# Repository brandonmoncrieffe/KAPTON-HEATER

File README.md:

## Kapton Heater System for Oxidizer Tank Pressure Regulation

This system uses a 24V, 14.6A Kapton trace heater to regulate the pressure inside a nitrous oxide oxidizer tank, particularly in colder environments where vapor pressure drops below optimal levels. The heater is PWM-controlled via a high-current N-channel MOSFET, allowing for precise thermal regulation.

Designed by Brandon Moncriefe and Aslan Lauzon for QRET

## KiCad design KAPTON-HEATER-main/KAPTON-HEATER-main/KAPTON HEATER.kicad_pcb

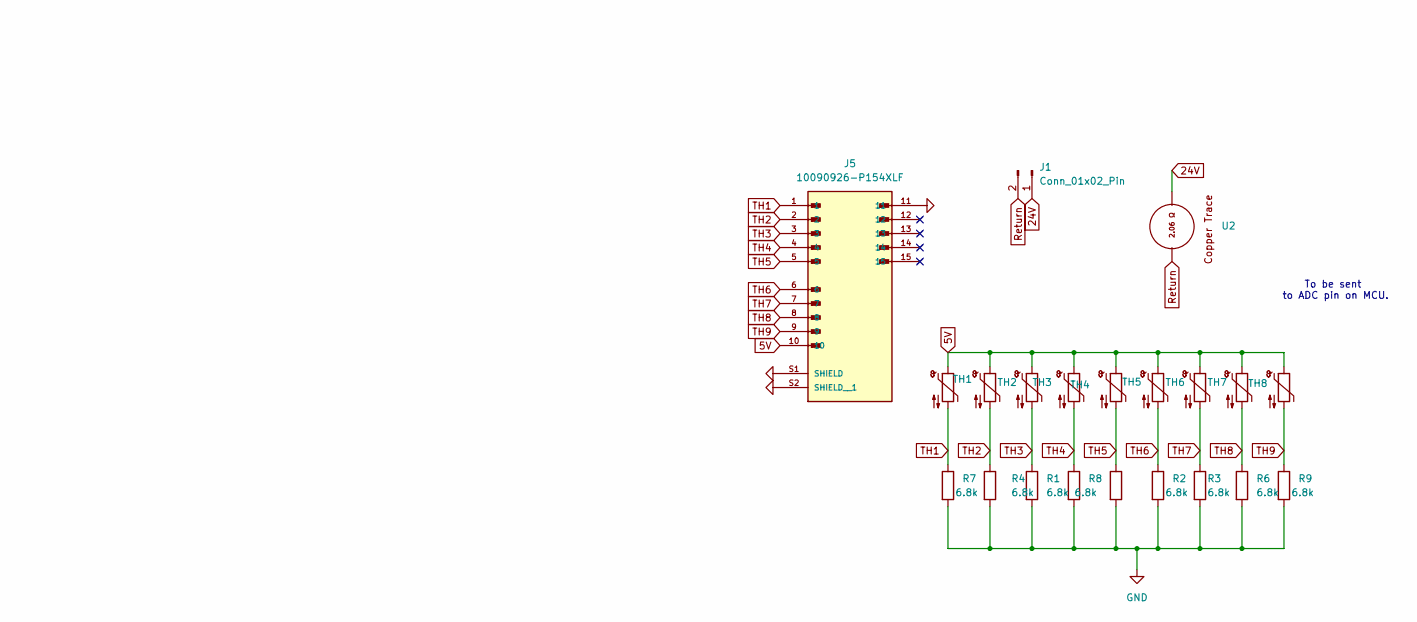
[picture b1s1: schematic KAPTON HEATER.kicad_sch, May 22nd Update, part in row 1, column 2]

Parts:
J1: Conn_01x02_Pin; AMASS_XT60PW-M
J5: 10090926-P154XLF; AMPHENOL_10090926-P154XLF; PARTREV H
R1, R2, R3, R4, R5, R6, R7, R8, R9: 6.8k; R_0201_0603Metric
TH1, TH2, TH3, TH4, TH5, TH6, TH7, TH8, TH9: Thermistor_NTC; R_0402_1005Metric
U2: (no value)

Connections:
5V: J5.10, TH1.1, TH2.1, TH3.1, TH4.1, TH5.1, TH6.1, TH7.1, TH8.1, TH9.1
24V: J1.1 (S1), U2.
GND: J5.11, J5.S1 (SHIELD), J5.S2 (SHIELD__1), R1.2, R2.2, R3.2, R4.2, R5.2, R6.2, R7.2, R8.2, R9.2
Return: J1.2 (S2), U2.
TH1: J5.1, R7.1, TH1.2
TH2: J5.2, R4.1, TH2.2
TH3: J5.3, R1.1, TH3.2
TH4: J5.4, R8.1, TH4.2
TH5: J5.5, R5.1, TH5.2
TH6: J5.6, R2.1, TH6.2
TH7: J5.7, R3.1, TH7.2
TH8: J5.8, R6.1, TH8.2
TH9: J5.9, R9.1, TH9.2

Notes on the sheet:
To be sent to ADC pin on MCU.

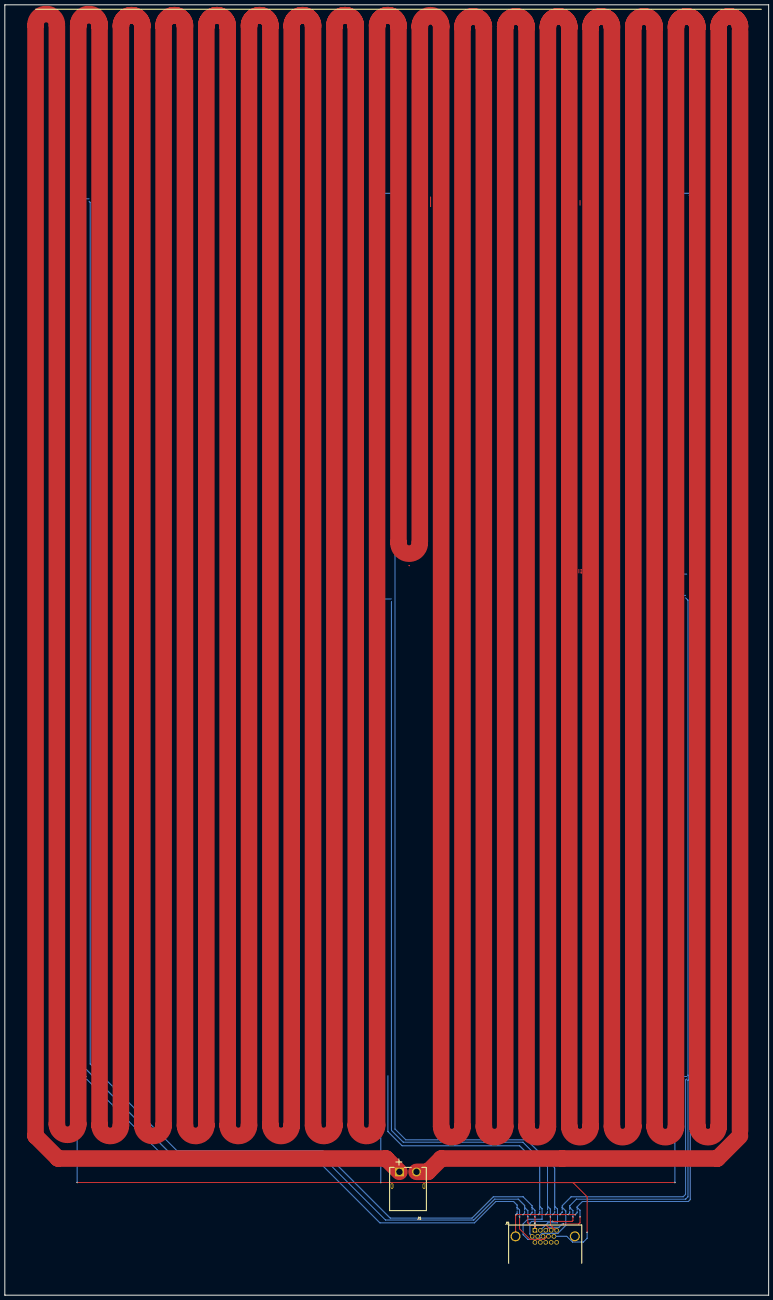
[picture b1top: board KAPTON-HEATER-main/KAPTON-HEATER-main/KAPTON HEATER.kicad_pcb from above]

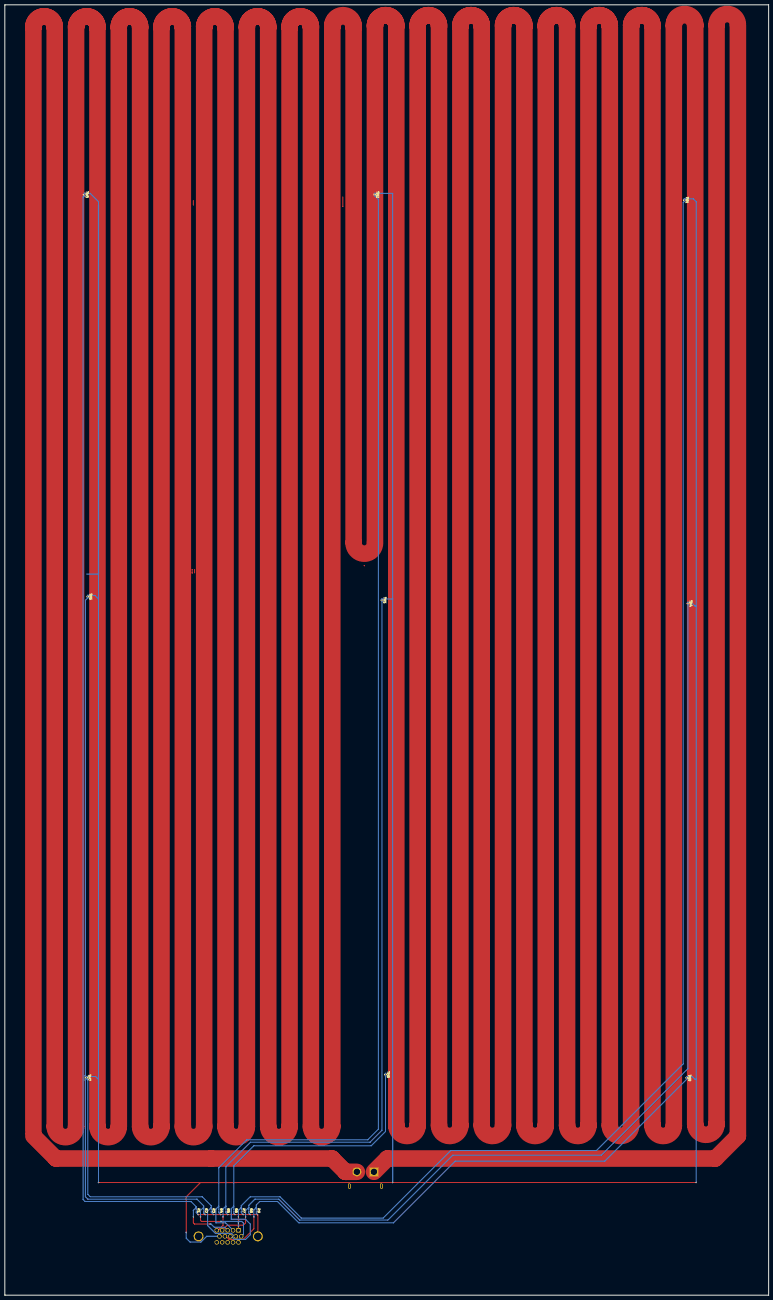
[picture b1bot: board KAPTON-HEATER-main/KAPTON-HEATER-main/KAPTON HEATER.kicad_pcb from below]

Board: 2 copper layers, 322.0 x 544.0 mm, 20 parts (18 on the bottom side), 11 nets.

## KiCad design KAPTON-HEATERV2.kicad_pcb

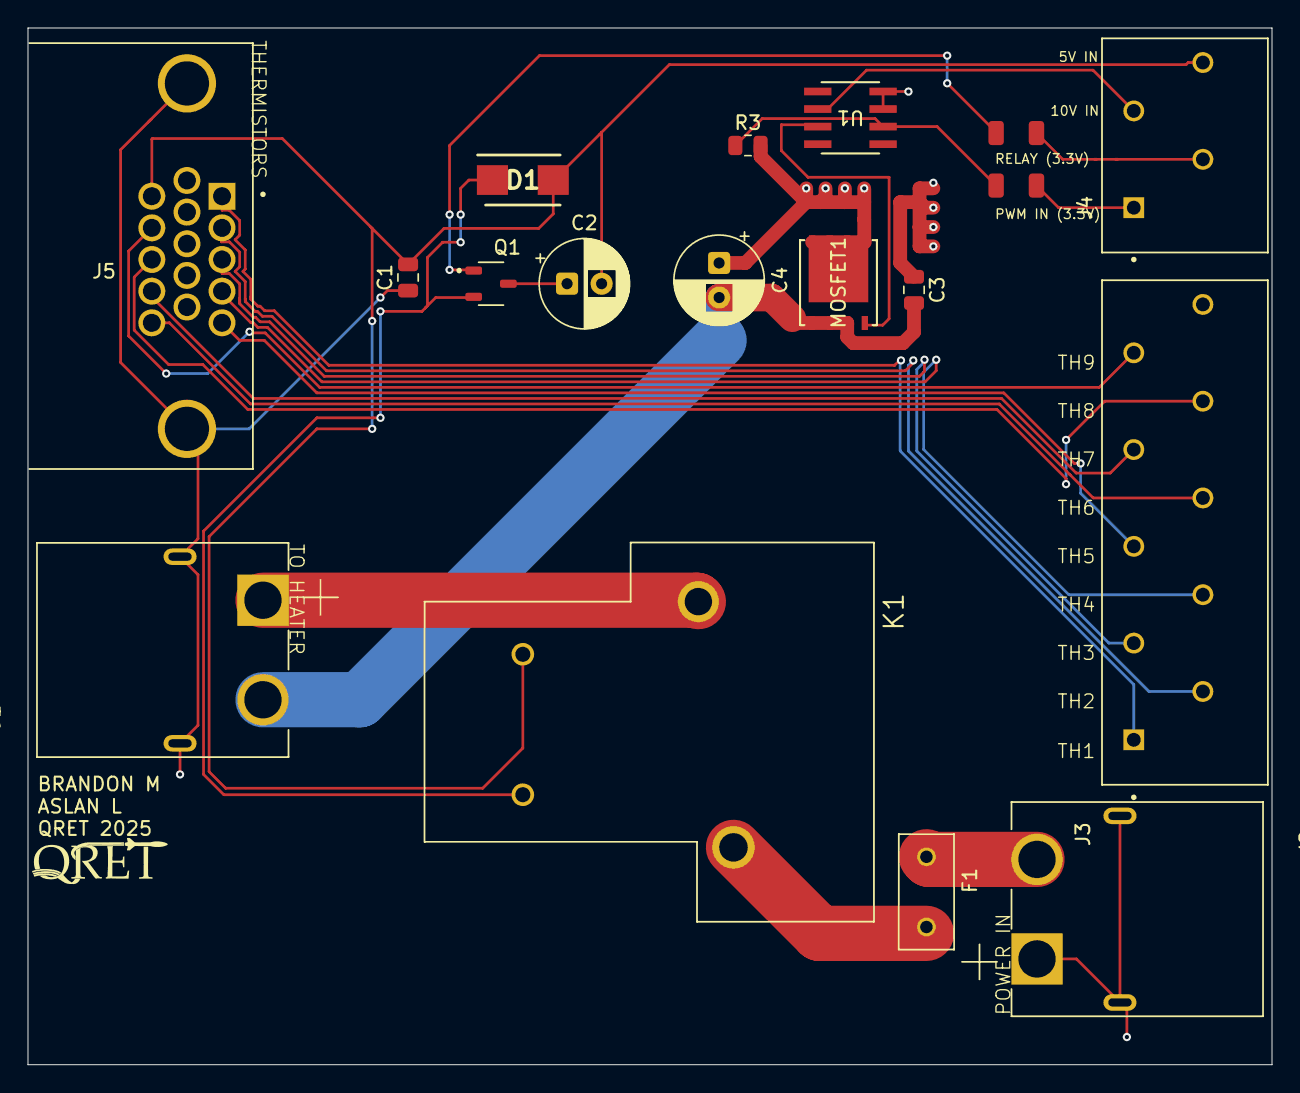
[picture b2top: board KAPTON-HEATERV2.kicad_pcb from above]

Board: 2 copper layers, 90.0 x 75.0 mm, 18 parts (0 on the bottom side), 22 nets.

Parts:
C1: C0.1uf; C_0805_2012Metric
C2: C47uf; CP_Radial_D6.3mm_P2.50mm
C3: C1uf; C_0805_2012Metric
C4: C10uf; CP_Radial_D6.3mm_P2.50mm
D1: MBRS1100T3G; DIOM5436X247N
F1: 20A Fuse; FUSRR508W60L835T400H810
J1, J2: XT60PW-M; AMASS_XT60PW-M
J3: 1985276; PHOENIX_1985276
J4: 1985218; TE_1985218
J5: 10090926-P154XLF; AMPHENOL_10090926-P154XLF
K1: 1-1393210-8; RELAY_1-1393210-8
MOSFET1: SIR462DP-T1-GE3; POWERPAK_SO-8_SINGLE_VIS
Q1: AO3400A; SOT95P280X125-3N
R1, R2: 100; R_1206
R3: R100k; R_0805_2012Metric
U1: TC4427ACOA; SOIC8-N_MC_MCH

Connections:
5V: C1.2, C2.2, D1.2 (A), J4.4, J5.11, K1.1
10V: J4.3, U1.6 (VDD)
10V PWM: MOSFET1.4, U1.7 (OUT_A)
/24V: J1.1, K1.4
/24VIN: F1.1, J2.2
/24VIN2: F1.2, K1.3
GND: C1.1, C2.1, C3.1, C4.1, J2.1, J2.S1, J2.S2, J5.S1 (SHIELD), J5.S2 (SHIELD__1), MOSFET1.5, MOSFET1.6, MOSFET1.7, MOSFET1.8, Q1.3, R3.2, U1.3 (GND), U1.4 (INPUT_B)
unnamed: D1.1 (K), K1.2, Q1.2
unnamed: C3.2, C4.2, J1.2, MOSFET1.1, MOSFET1.2, MOSFET1.3
unnamed: Q1.1, R1.2
unnamed: R2.2, R3.1, U1.2 (INPUT_A)
PWM: J4.1, R2.1
RELAY: J4.2, R1.1
TH1: J3.1, J5.1
TH2: J3.2, J5.2
TH3: J3.3, J5.3
TH4: J3.4, J5.4
TH5: J3.5, J5.5
TH6: J3.6, J5.15
TH7: J3.7, J5.14
TH8: J3.8, J5.13
TH9: J3.9, J5.12

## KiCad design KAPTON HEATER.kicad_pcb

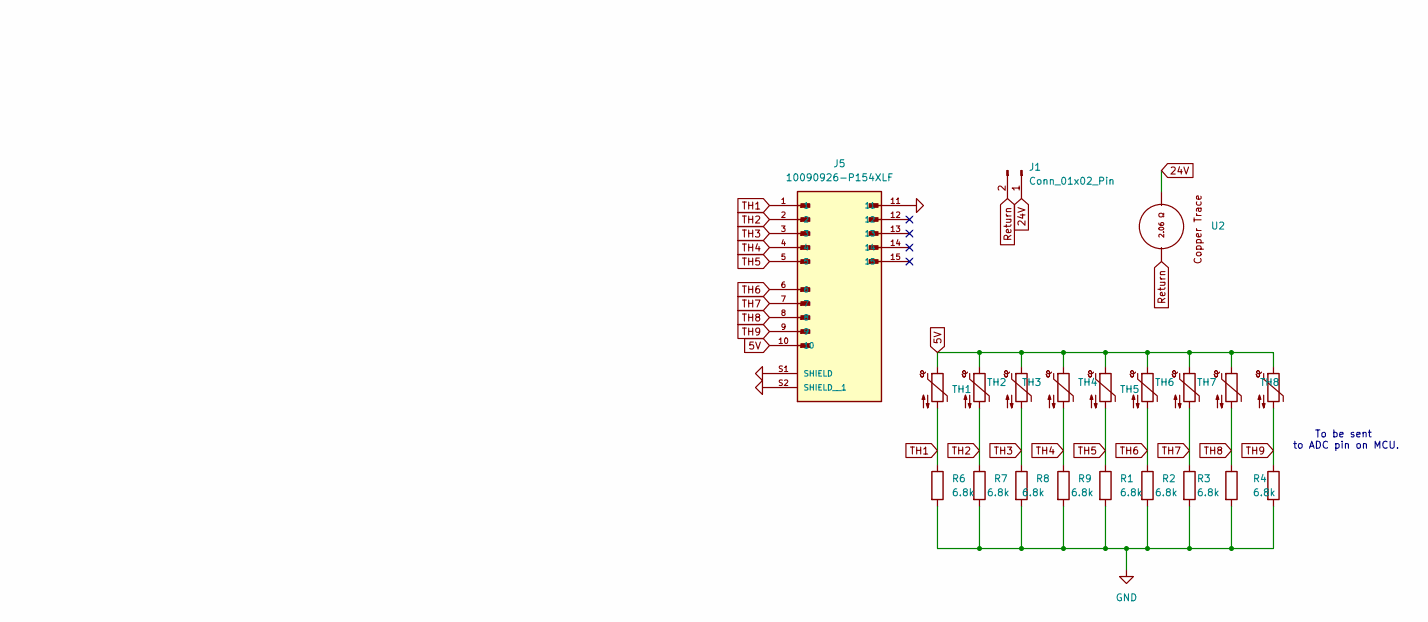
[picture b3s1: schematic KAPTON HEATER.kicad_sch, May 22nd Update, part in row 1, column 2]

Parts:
J1: Conn_01x02_Pin; AMASS_XT60PW-M
J5: 10090926-P154XLF; AMPHENOL_10090926-P154XLF; PARTREV H
R1, R2, R3, R4, R5, R6, R7, R8, R9: 6.8k; R_0201_0603Metric
TH1, TH2, TH3, TH4, TH5, TH6, TH7, TH8, TH9: Thermistor_NTC; R_Array_SIP4
U2: (no value)

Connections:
5V: J5.10, TH1.1, TH2.1, TH3.1, TH4.1, TH5.1, TH6.1, TH7.1, TH8.1, TH9.1
24V: J1.1 (S1), U2.
GND: J5.11, J5.S1 (SHIELD), J5.S2 (SHIELD__1), R1.2, R2.2, R3.2, R4.2, R5.2, R6.2, R7.2, R8.2, R9.2
Return: J1.2 (S2), U2.
TH1: J5.1, R6.1, TH1.2
TH2: J5.2, R7.1, TH2.2
TH3: J5.3, R8.1, TH3.2
TH4: J5.4, R9.1, TH4.2
TH5: J5.5, R1.1, TH5.2
TH6: J5.6, R2.1, TH6.2
TH7: J5.7, R3.1, TH7.2
TH8: J5.8, R4.1, TH8.2
TH9: J5.9, R5.1, TH9.2

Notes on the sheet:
To be sent to ADC pin on MCU.

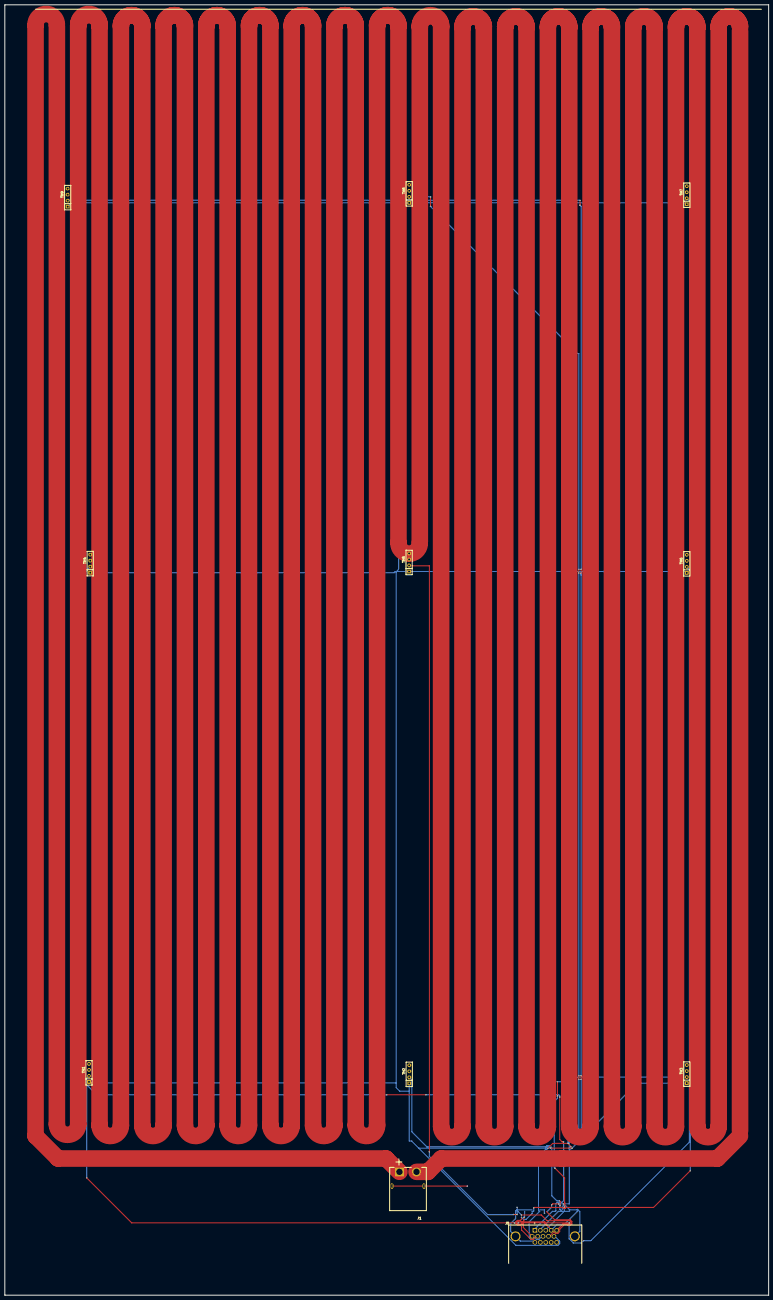
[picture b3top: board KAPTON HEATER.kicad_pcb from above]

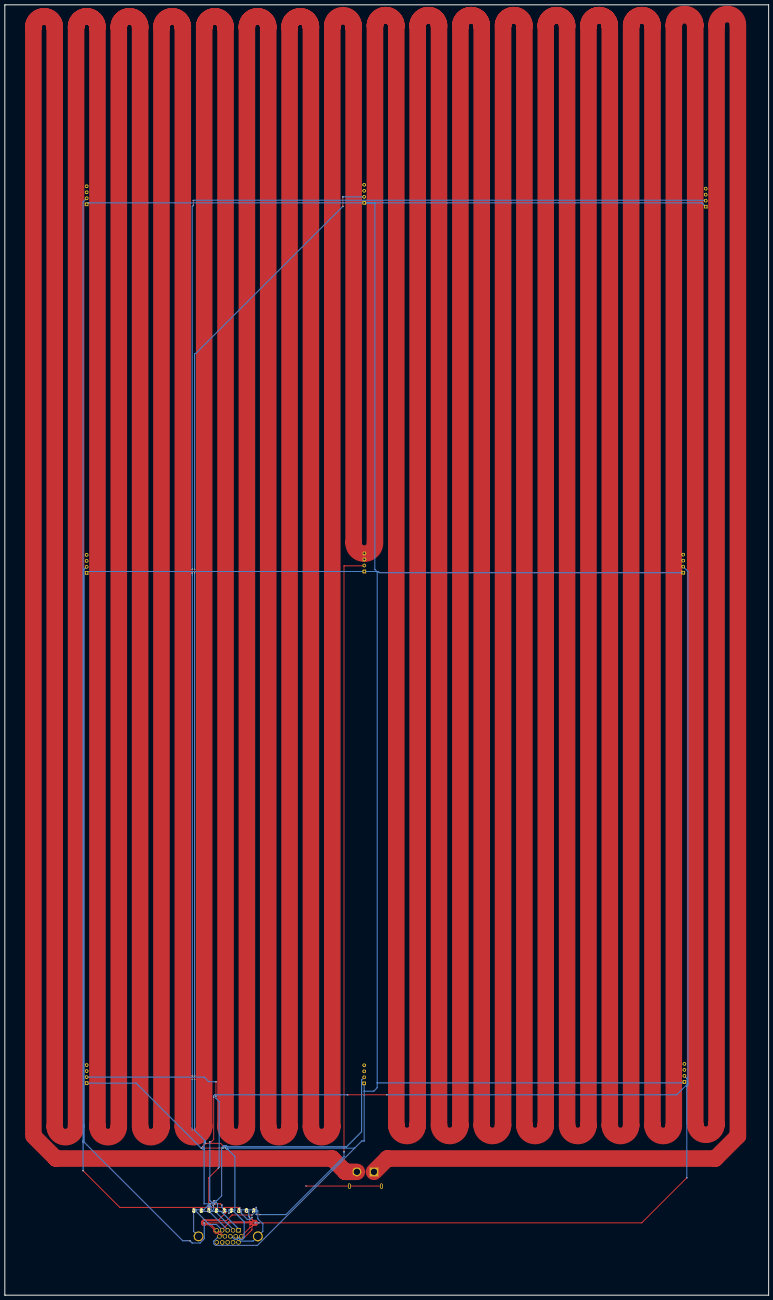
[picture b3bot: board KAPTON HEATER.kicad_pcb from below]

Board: 2 copper layers, 322.0 x 544.0 mm, 20 parts (9 on the bottom side), 11 nets.

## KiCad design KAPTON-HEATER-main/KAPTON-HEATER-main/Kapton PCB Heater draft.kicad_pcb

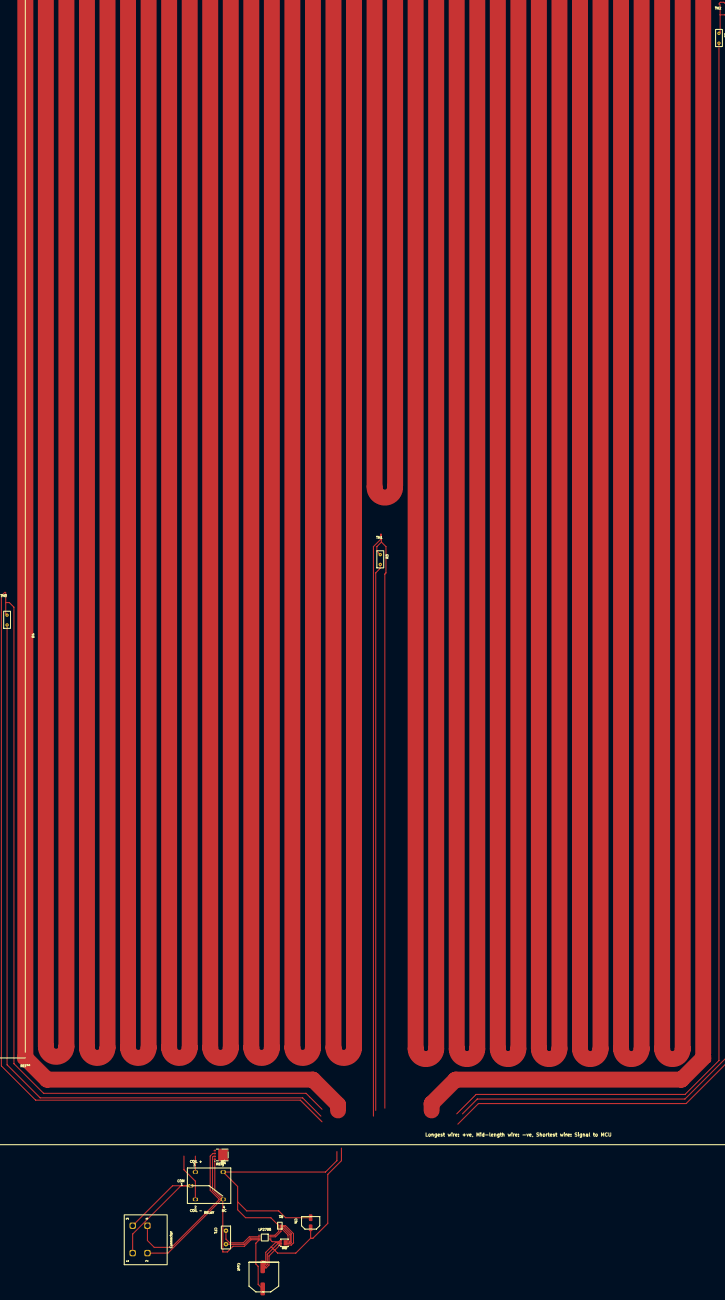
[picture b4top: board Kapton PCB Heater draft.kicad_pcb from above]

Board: 2 copper layers, 14 parts (0 on the bottom side), 6 nets.

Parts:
CF1: C; Cf
Cin: C; Cin
Connector: Conector; Connector
Cout: C; Cout
LP2795: SOIC-8
PFET: PFET
R1: CRE2512-FZ-R003E-3; PFET Resistor
R2, R3, R4: R; Thermistor Resistors
RELAY: Relay
TH1, TH2, TH3: Thermistor_NTC; Thermistor

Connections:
unnamed: LP2795.7 (CURR_LIM), PFET.6, PFET.7, PFET.8, PFET.9, R1.1
unnamed: LP2795.5 (GATE), PFET.4 (GATE)
unnamed: CF1.1, Cin.2, Connector.2, Connector.4, Cout.1, Cout.2, LP2795.2 (FEEDBACK), LP2795.4 (GROUND), PFET.1, PFET.2, PFET.3, R2.2, R3.2, R4.2, RELAY.4 (N/C), TH1.1, TH1.2, TH2.1, TH2.2, TH3.1, TH3.2
unnamed: CF1.2, LP2795.3 (COMP)
unnamed: Cin.1, LP2795.8 (INPUT), R1.2, RELAY.5
unnamed: Connector.1, Connector.3, RELAY.1 (COIL)

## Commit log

2025-05-22 Kapton
2025-05-27 Commit 3
    Connection from rigid to flex sections added. 12 Pin connector for thermistor signal(s) and power.
2025-05-27 Commit 3.1
2025-05-28 Commit 3.2
    Floated GND
2025-05-29 redid the project file. big changes to schematic
    Added flyback diodes and decoupling capacitors. designed v1 of the board
2025-05-30 Heater PCB complete
2025-05-30 fixing repo
2025-05-31 Done?
2025-05-31 forgot to save
2025-06-08 Trace
